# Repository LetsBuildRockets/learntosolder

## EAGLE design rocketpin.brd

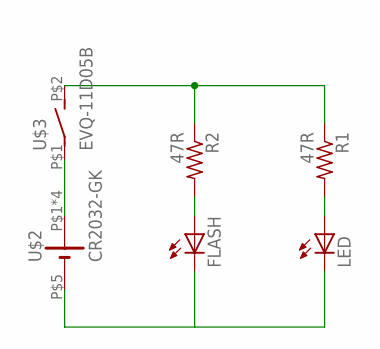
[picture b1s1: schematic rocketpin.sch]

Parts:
FLASH: LED5MM
LED: LED5MM
R1, R2: 47R; 0207/10
U$2: CR2032-GK; BAT-HLD-001-THM
U$3: EVQ-11D05B; SPST-5MM

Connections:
GND: FLASH.K (C), LED.K (C), U$2.P$5 (-)
unnamed: R1.1, R2.1, U$3.P$2 (S)
unnamed: LED.A, R1.2
unnamed: FLASH.A, R2.2
unnamed: U$2.P$1 (+), U$2.P$2 (+), U$2.P$3 (+), U$2.P$4 (+), U$3.P$1

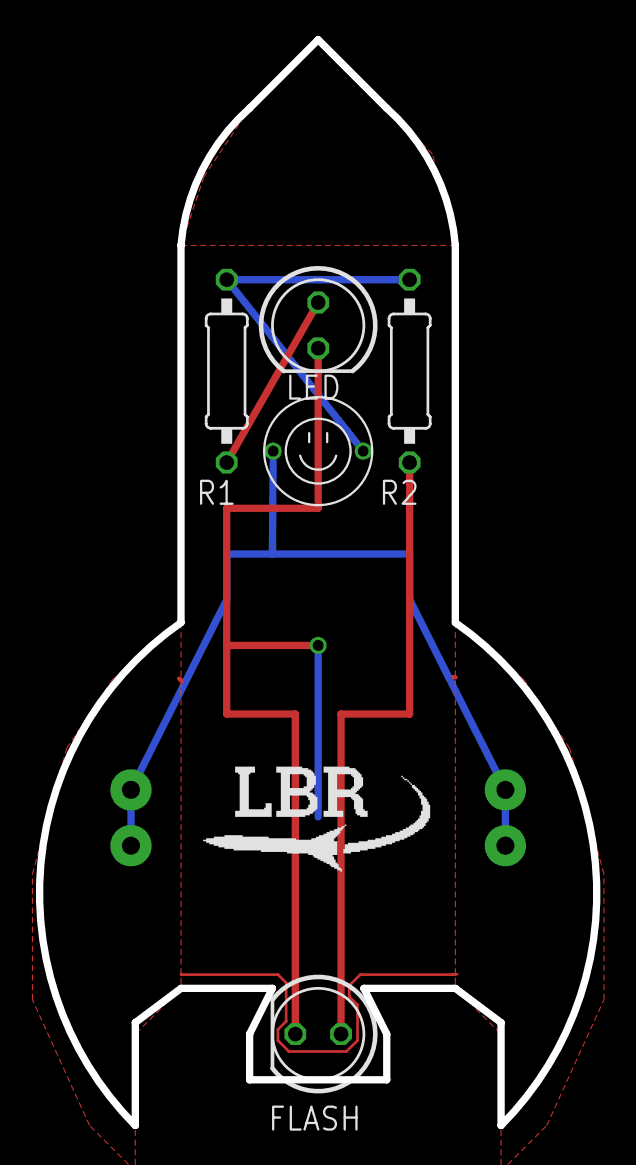
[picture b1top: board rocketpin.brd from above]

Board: 2 copper layers, 30.9 x 60.3 mm, 7 parts (1 on the bottom side), 5 nets.

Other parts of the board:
U$1: LOGO-0.50"

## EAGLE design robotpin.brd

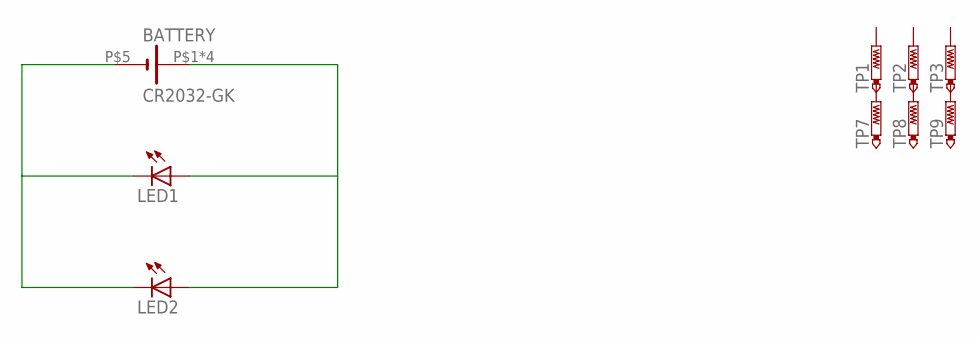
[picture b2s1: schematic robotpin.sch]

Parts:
BATTERY: CR2032-GK; BAT-HLD-001-THM
LED1, LED2: LED5MM
TP1, TP2, TP3, TP7, TP8, TP9: PTR1TP12R; TP12R

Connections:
unnamed: BATTERY.P$1 (+), BATTERY.P$2 (+), BATTERY.P$3 (+), BATTERY.P$4 (+), LED1.A, LED2.A
unnamed: BATTERY.P$5 (-), LED1.K (C), LED2.K (C)

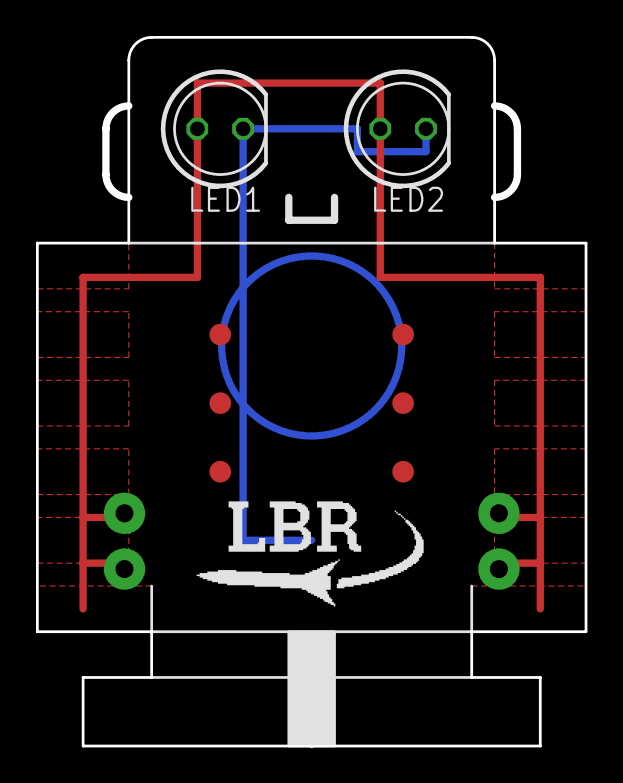
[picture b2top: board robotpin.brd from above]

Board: 2 copper layers, 30.2 x 39.1 mm, 10 parts (1 on the bottom side), 2 nets.

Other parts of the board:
U$2: LOGO-0.50"

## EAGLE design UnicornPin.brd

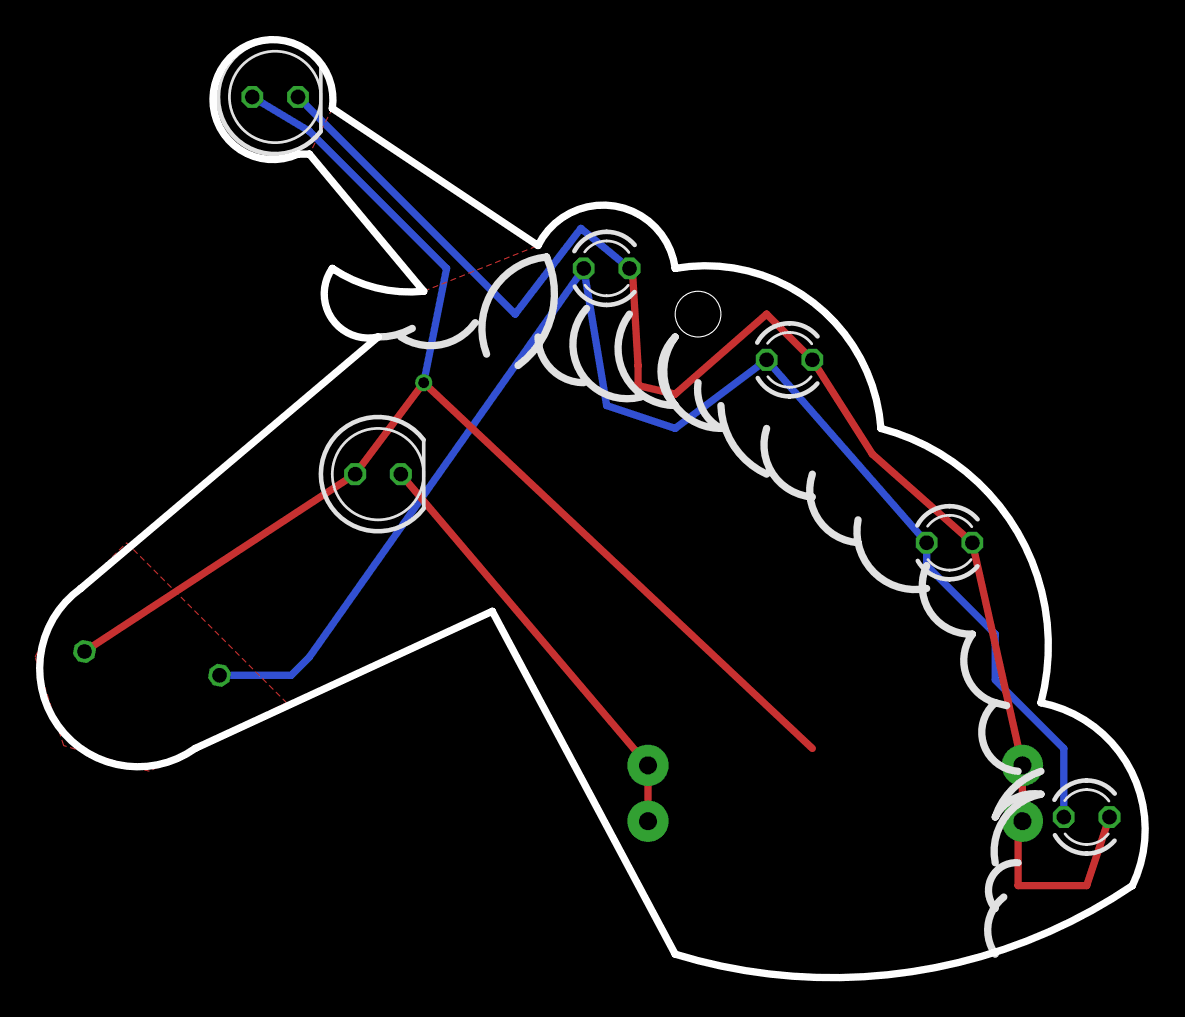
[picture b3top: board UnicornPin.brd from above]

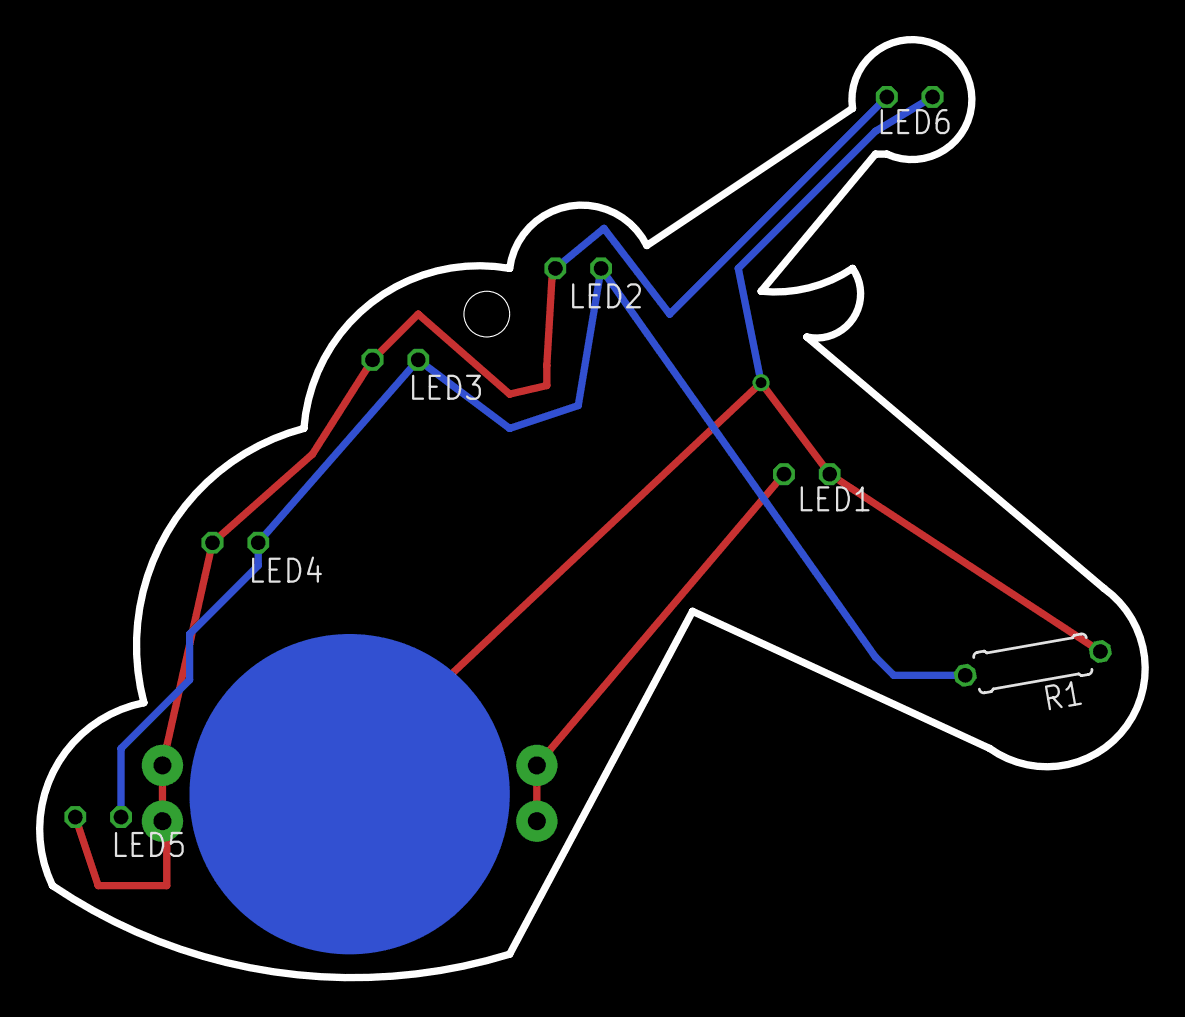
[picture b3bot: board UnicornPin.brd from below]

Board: 2 copper layers, 61.4 x 52.1 mm, 8 parts (2 on the bottom side), 3 nets.

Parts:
LED1, LED6: LED5MM
LED2, LED3, LED4, LED5: LED3MM
R1: 120R; 0207/7
U$1: CR2032-GK; BAT-HLD-001-THM

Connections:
unnamed: LED1.A, LED6.A, R1.1, U$1.P$5
unnamed: LED1.K, LED2.K, LED3.K, LED4.K, LED5.K, LED6.K, U$1.P$1, U$1.P$2, U$1.P$3, U$1.P$4
unnamed: LED2.A, LED3.A, LED4.A, LED5.A, R1.2

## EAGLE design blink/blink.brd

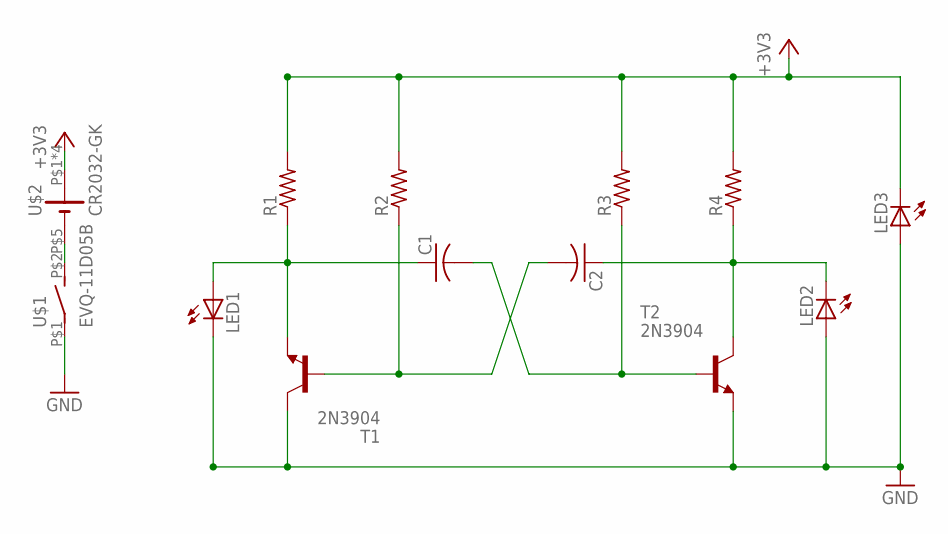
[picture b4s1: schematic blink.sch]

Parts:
C1, C2: C-US025-030X050; C025-030X050
LED1, LED2: LED3MM
LED3: LED5MM
R1, R2, R3, R4: R-US_0207/7; 0207/7
T1, T2: 2N3904; TO92
U$1: EVQ-11D05B; SPST-5MM
U$2: CR2032-GK; BAT-HLD-001-THM

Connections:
+3V3: LED3.K (C), R1.2, R2.2, R3.2, R4.2, U$2.P$1 (+), U$2.P$2 (+), U$2.P$3 (+), U$2.P$4 (+)
GND: LED1.K (C), LED2.A, LED3.A, T1.1 (C), T2.3 (E), U$1.P$1
unnamed: C1.1, LED1.A, R1.1, T1.3 (E)
unnamed: U$1.P$2 (S), U$2.P$5 (-)
unnamed: C2.1, LED2.K (C), R4.1, T2.1 (C)
unnamed: C1.2, R3.1, T2.2 (B)
unnamed: C2.2, R2.1, T1.2 (B)

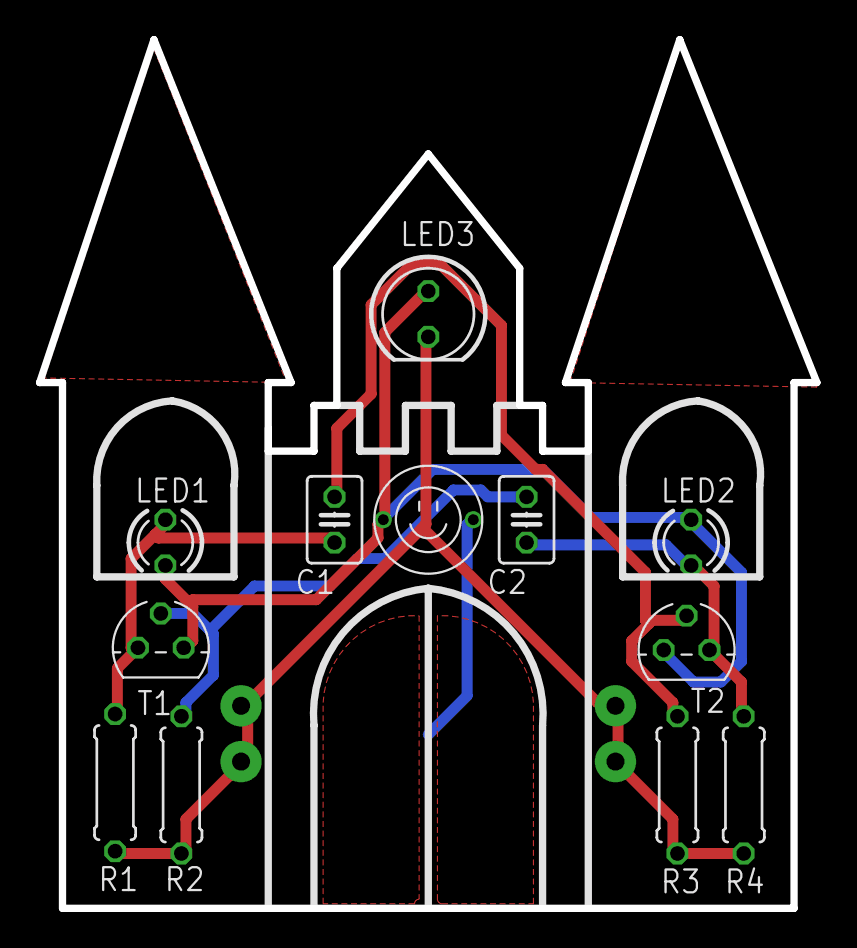
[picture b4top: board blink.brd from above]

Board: 2 copper layers, 43.2 x 48.3 mm, 13 parts (1 on the bottom side), 7 nets.

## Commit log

2017-04-05 Add rocket pin files
2017-06-19 v2, ordered from seeed studio spring 2017
2017-07-26 add robot pin boards. V1. has not been ordered yet
2017-07-26 unicorn pin v1, work in progress
2017-07-26 modified unicorn board
2017-07-26 added unicorn board
2017-07-28 final unicorn design
2017-07-28 prettify robot pin
2017-07-28 add oshpark previews for robot board
2017-07-28 removed names on robot schematic
2017-07-28 committing unicorn and robot pin
2017-08-09 changed size to add button
2017-08-09 didn't change robot but did?
2017-08-09 modify rocket pin
2017-08-09 add more stuff to ignore
2017-08-09 designed castle
2017-08-11 modified blink board
2017-09-11 maybe modified blink and robot board?
2017-09-11 routed unicorn board to fit the new schematic
2017-09-11 changed unicorn schematic so that all leds are in parallel with each other
